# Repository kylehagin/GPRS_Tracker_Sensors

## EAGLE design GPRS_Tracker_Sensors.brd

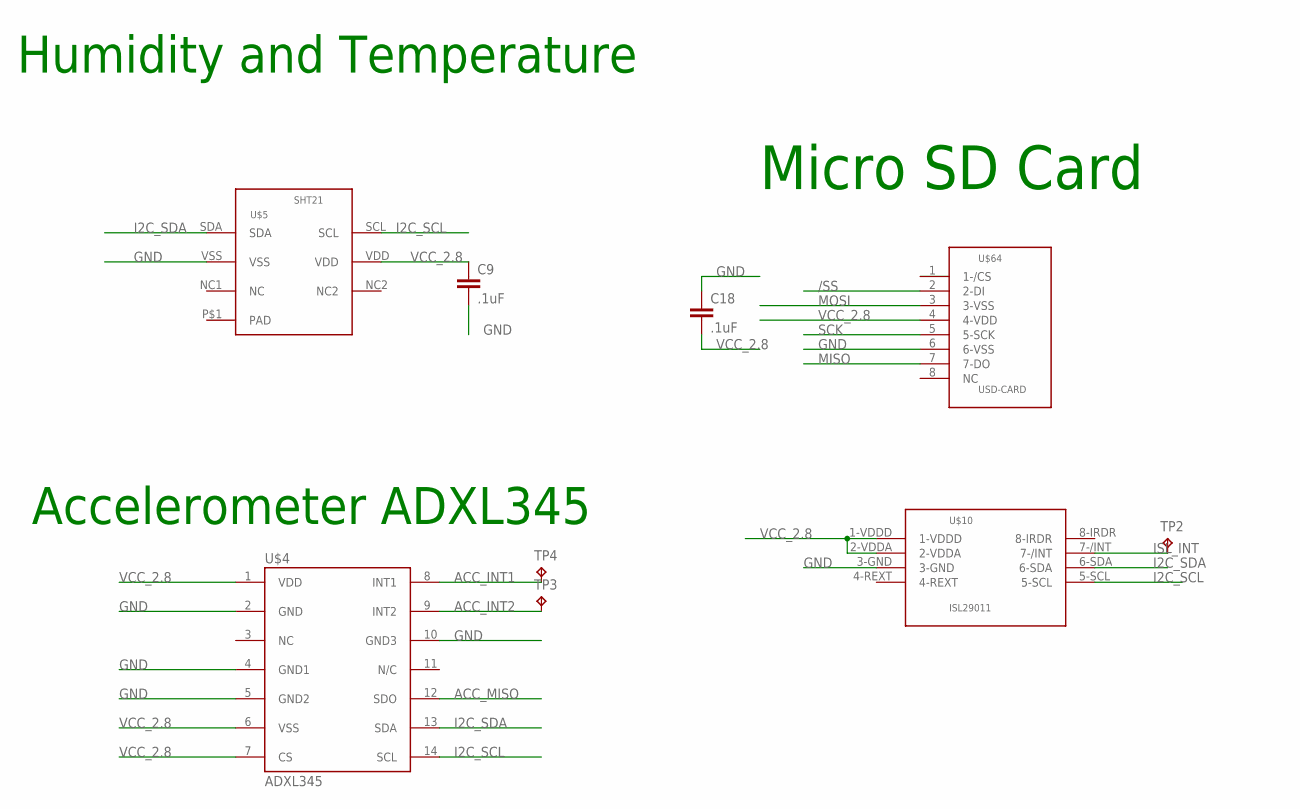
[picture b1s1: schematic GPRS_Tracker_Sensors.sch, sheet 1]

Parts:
C9, C18: .1uF; C0402
TP2: TPTP08R; TP08R
TP3, TP4: TPTP06R; TP06R
U$4: ADXL345; LGA14
U$5: SHT21
U$10: ISL29011
U$64: USD-CARD; 502774-0891

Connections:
/SS: U$64.2 (2-DI)
ACC_INT1: TP4.TP, U$4.8 (INT1)
ACC_INT2: TP3.TP, U$4.9 (INT2)
ACC_MISO: U$4.12 (SDO)
GND: C9.2, C18.1, U$4.2 (GND), U$4.4 (GND1), U$4.5 (GND2), U$4.10 (GND3), U$5.VSS, U$10.3-GND, U$64.6 (6-VSS); also elsewhere on the board
I2C_SCL: U$4.14 (SCL), U$5.SCL, U$10.5-SCL
I2C_SDA: U$4.13 (SDA), U$5.SDA, U$10.6-SDA
ISL_INT: TP2.TP, U$10.7-/INT
MISO: U$64.7 (7-DO)
MOSI: U$64.3 (3-VSS)
SCK: U$64.5 (5-SCK)
VCC_2.8: C9.1, C18.2, U$4.1 (VDD), U$4.6 (VSS), U$4.7 (CS), U$5.VDD, U$10.1-VDDD, U$10.2-VDDA, U$64.4 (4-VDD); also elsewhere on the board

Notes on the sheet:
Micro SD Card
Accelerometer ADXL345
Humidity and Temperature

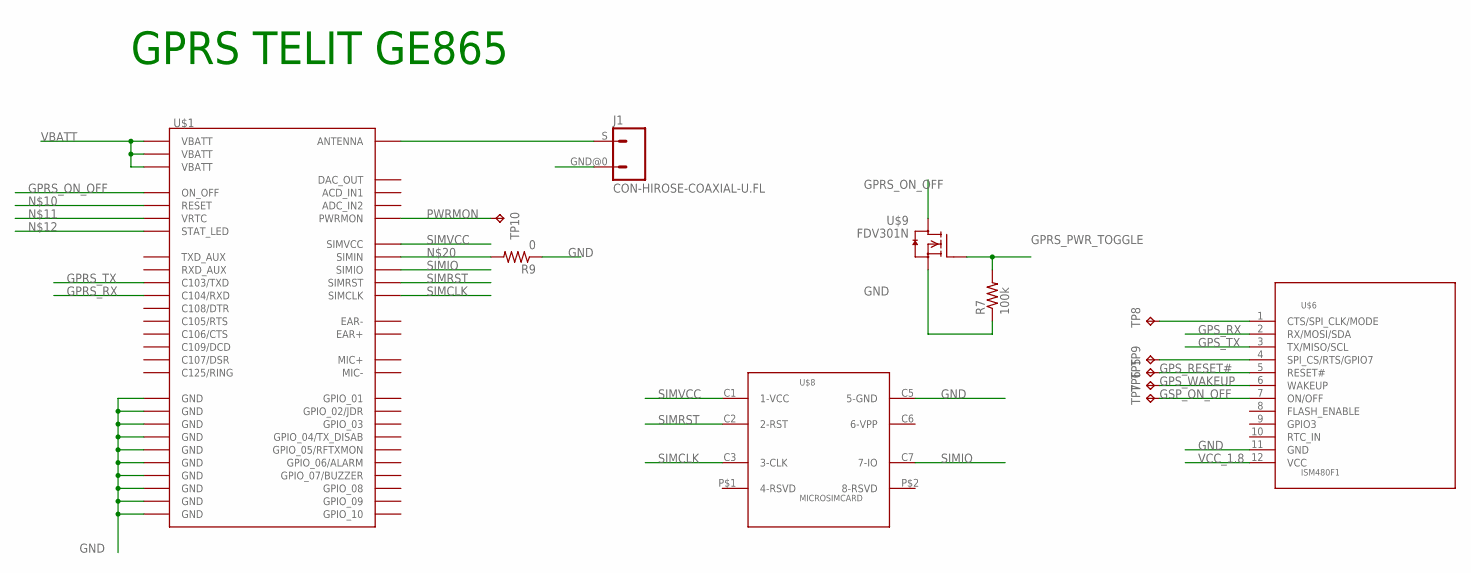
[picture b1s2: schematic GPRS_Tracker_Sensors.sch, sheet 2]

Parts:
J1: CON-HIROSE-COAXIAL-U.FL; CON-U.FL
R7: 100k; R0402
R9: 0; R0402
TP5, TP6, TP7, TP8, TP9, TP10: TPTP06R; TP06R
U$1: GE865
U$6: ISM480F1; 20488-012E-01
U$8: MICROSIMCARD; FMS006-5000-0
U$9: FDV301N; SOT23

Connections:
GND: R7.1, R9.1, U$1.C2 (GND), U$1.C7 (GND), U$1.E5 (GND), U$1.E7 (GND), U$1.G1 (GND), U$1.G3 (GND), U$1.G4 (GND), U$1.G5 (GND), U$1.H3 (GND), U$1.H6 (GND), U$6.11 (GND), U$8.C5 (5-GND), U$9.2 (S); also elsewhere on the board
GPRS_ON_OFF: U$1.B1 (ON_OFF), U$9.3 (D)
GPRS_PWR_TOGGLE: R7.2, U$9.1 (G)
GPRS_RX: U$1.A4 (C104/RXD)
GPRS_TX: U$1.A3 (C103/TXD)
GPS_RESET#: TP5.TP, U$6.5 (RESET#)
GPS_RX: U$6.2 (RX/MOSI/SDA)
GPS_TX: U$6.3 (TX/MISO/SCL)
GPS_WAKEUP: TP6.TP, U$6.6 (WAKEUP)
GSP_ON_OFF: TP7.TP, U$6.7 (ON/OFF)
unnamed: J1.S (1), U$1.H5 (ANTENNA)
unnamed: TP8.TP, U$6.1 (CTS/SPI_CLK/MODE)
unnamed: TP9.TP, U$6.4 (SPI_CS/RTS/GPIO7)
unnamed: R9.2, U$1.B7 (SIMIN)
PWRMON: TP10.TP, U$1.E2 (PWRMON)
SIMCLK: U$1.A5 (SIMCLK), U$8.C3 (3-CLK)
SIMIO: U$1.A6 (SIMIO), U$8.C7 (7-IO)
SIMRST: U$1.A8 (SIMRST), U$8.C2 (2-RST)
SIMVCC: U$1.A7 (SIMVCC), U$8.C1 (1-VCC)
VBATT: U$1.F1 (VBATT), U$1.F2 (VBATT), U$1.F3 (VBATT); also elsewhere on the board
VCC_1.8: U$6.12 (VCC); also elsewhere on the board

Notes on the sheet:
GPRS TELIT GE865

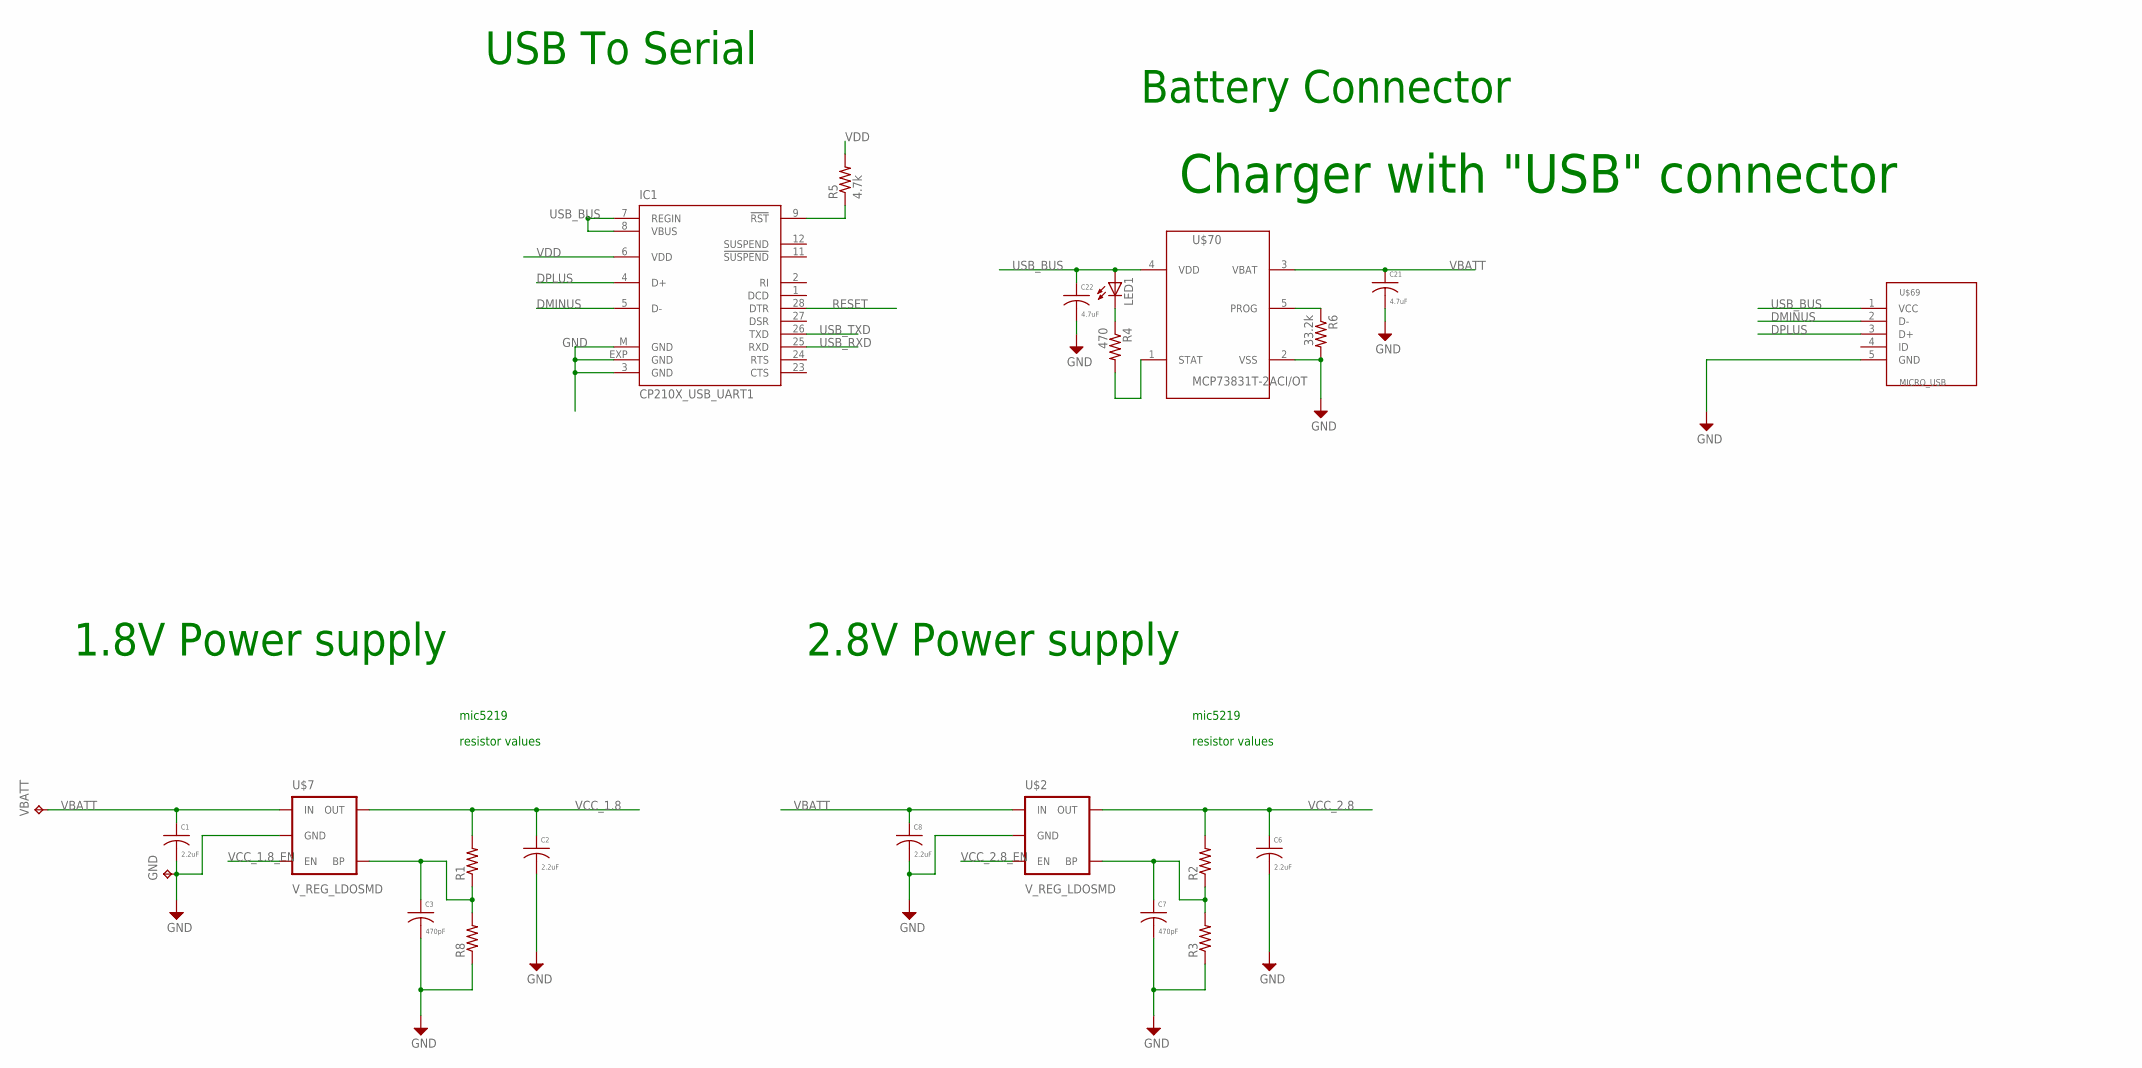
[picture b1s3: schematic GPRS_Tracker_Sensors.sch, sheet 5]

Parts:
C1, C2, C6, C8: 2.2uF; C0603
C3, C7: 470pF; C0402
C21, C22: 4.7uF; C0603
GND: TPTP15R; TP15R
IC1: CP210X_USB_UART1; MLP28
LED1: LEDCHIP-LED0603; CHIP-LED0603
R1, R2, R3, R8: R-US_R0402; R0402
R4: 470; R0402
R5: 4.7k; R0402
R6: 33.2k; R0402
U$2, U$7: V_REG_LDOSMD; SOT23-5
U$69: MICRO_USB
U$70: MCP73831T-2ACI/OT; SOT23-5L
VBATT: TPTP15R; TP15R

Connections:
CHG_STAT: R4.2, U$70.1 (STAT)
DMINUS: IC1.5 (D-), U$69.2 (D-)
DPLUS: IC1.4 (D+), U$69.3 (D+)
GND: C1.2, C2.2, C3.2, C6.2, C7.2, C8.2, C21.2, C22.2, GND.TP, IC1.3 (GND), IC1.EXP (GND), IC1.M (GND), R3.1, R6.2, R8.1, U$2.2 (GND), U$7.2 (GND), U$69.5 (GND), U$70.2 (VSS); also elsewhere on the board
unnamed: C3.1, R1.1, R8.2, U$7.4 (BP)
unnamed: C7.1, R2.1, R3.2, U$2.4 (BP)
unnamed: IC1.9 (!RST), R5.1
unnamed: LED1.C, R4.1
unnamed: R6.1, U$70.5 (PROG)
RESET: IC1.28 (DTR)
USB_BUS: C22.1, IC1.7 (REGIN), IC1.8 (VBUS), LED1.A, U$69.1 (VCC), U$70.4 (VDD)
USB_RXD: IC1.25 (RXD)
USB_TXD: IC1.26 (TXD)
VBATT: C1.1, C8.1, C21.1, U$2.1 (IN), U$7.1 (IN), U$70.3 (VBAT), VBATT.TP; also elsewhere on the board
VCC_1.8: C2.1, R1.2, U$7.5 (OUT); also elsewhere on the board
VCC_1.8_EN: U$7.3 (EN)
VCC_2.8: C6.1, R2.2, U$2.5 (OUT); also elsewhere on the board
VCC_2.8_EN: U$2.3 (EN)
VDD: IC1.6 (VDD), R5.2

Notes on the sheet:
mic5219
resistor values
1.8V Power supply
2.8V Power supply
USB To Serial
Battery Connector
Charger with "USB" connector

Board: 2 copper layers, 45 parts (17 on the bottom side), 33 nets, no tracks yet.
